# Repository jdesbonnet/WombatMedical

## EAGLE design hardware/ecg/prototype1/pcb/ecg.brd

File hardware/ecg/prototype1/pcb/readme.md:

# ECG PCB

## Notes

JP2 is UART, used for issuing commands, downloading data and upgrading firmware. Firmware updates require the MCU to enter bootloader mode at startup using the DTR, RTS lines (connect DTR to RESET and RTS to ISPEnter pin). Note that connecting to the device with picocom while DTR connected will cause the device to reset on connect. Disconnect RESET line during normal use.

Pin 1 = GND, pin 2 = ISPEnter, pin 3 = Vdd, pin 4 = TXD, pin 5 = RXD, pin 6 = RESET.  

JP4 is a convenient point to access the SPI bus from MCU to ECG front end IC. Pin 1 = DOUT, pin 2 = DIN, pin 3 = SCLK, pin 4 CS. Pin 5, 6 was NC 
on the PCB but on prototype bodge wire was used to connect VCC and GND. 

JP3 analog ECG lines. Pin 1 = RLDOUT, pin 2 = IN1N, pin 3 = IN1P.

JP5 power.

## Bugs

There were some bugs on the board:

1. ADS1929R missing crucial feedback from RLDOUT via 1Mohm resistor with 1.5nF capacitor in parallel with resistor.
Ref datasheet figure 52. Not clear if this bug could have been worked around in software.

2. CLKSEL needs to be tied high to enable internal clock.

3. Coin cell solder mask wrong.

4. It was a mistake not to break out a Serial Wire Debug header.

## Notes for next version

* Move to ARM Cortex-M0+ MCU eg LPC824
* Add SPI flash chip for storage
* Crystal for more accurate off-line time keeping
* Modular radio (allow for RFMxx, or ESP-0x or bluetooth modules)
* Smaller PCB area, thinner (all SMD).
* Use 3.5mm audio jack for 3 wire ECG connector

## Firmware

Firmware is available at this repository:
https://github.com/jdesbonnet/LPC1114_ECG_firmware

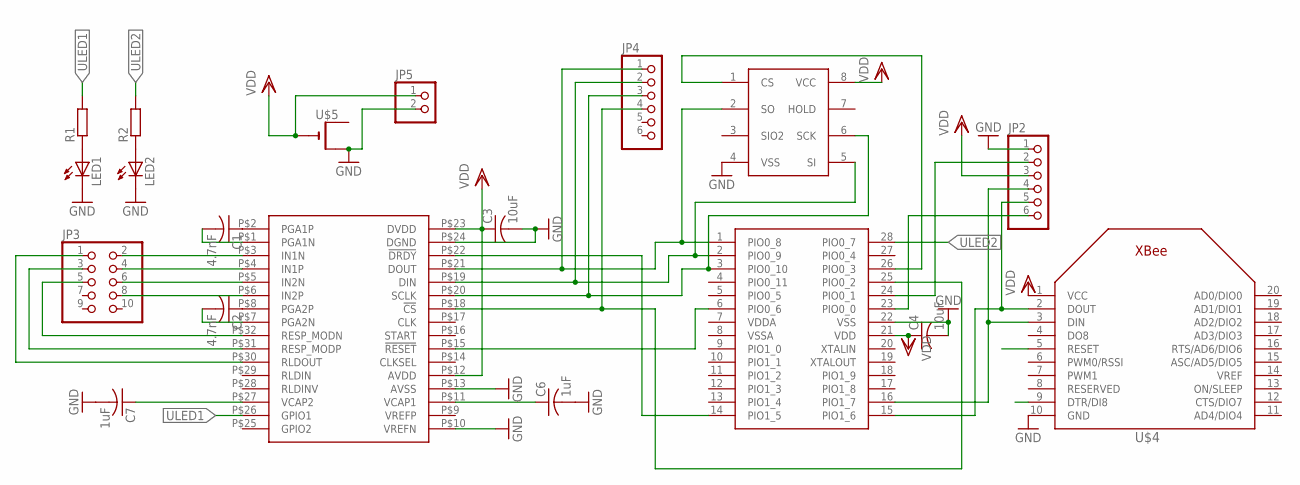
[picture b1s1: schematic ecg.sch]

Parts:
C1, C2: 4.7nF; C0805
C3, C4: 10uF; C0805
C6, C7: 1uF; C0805
JP2, JP4: PINHD-1X6; 1X06
JP3: PINHD-2X5; 2X05
JP5: PINHD-1X2; 1X02
LED1, LED2: LED3MM
R1, R2: R-EU_R0805; R0805
U$1: ADS1929R; TQFP32
U$2: LPC1114FN28; DIL28-6
U$3: 23A1024; DIL08
U$4: XBEE
U$5: CR2032SMT; CR2032-SMD

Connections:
GND: C3.2, C4.2, C6.2, C7.2, JP2.1, JP5.2, LED1.K (C), LED2.K (C), U$1.P$10 (VREFN), U$1.P$13 (AVSS), U$1.P$24 (DGND), U$2.22 (VSS), U$3.4 (VSS), U$4.10 (GND), U$5.+$2 (+1)
unnamed: C1.1, U$1.P$2 (PGA1P)
unnamed: C1.2, U$1.P$1 (PGA1N)
unnamed: C2.1, U$1.P$8 (PGA2P)
unnamed: C2.2, U$1.P$7 (PGA2N)
unnamed: JP4.1, U$1.P$21 (DOUT), U$2.1 (PIO0_8), U$3.2 (SO)
unnamed: JP4.2, U$1.P$19 (DIN), U$2.2 (PIO0_9), U$3.5 (SI)
unnamed: JP4.3, U$1.P$20 (SCLK), U$2.3 (PIO0_10), U$3.6 (SCK)
unnamed: JP4.4, U$1.P$18 (!CS!), U$2.25 (PIO0_2)
unnamed: U$1.P$22 (!DRDY!), U$2.14 (PIO1_5)
unnamed: JP3.2, U$1.P$3 (IN1N)
unnamed: JP3.4, U$1.P$4 (IN1P)
unnamed: JP3.6, U$1.P$5 (IN2N)
unnamed: JP3.8, U$1.P$6 (IN2P)
unnamed: U$1.P$15 (!RESET!), U$2.6 (PIO0_6)
unnamed: JP3.5, U$1.P$32 (RESP_MODN)
unnamed: JP3.3, U$1.P$31 (RESP_MODP)
unnamed: JP3.1, U$1.P$30 (RLDOUT)
unnamed: JP2.6, U$2.23 (PIO0_0)
unnamed: U$2.26 (PIO0_3), U$3.1 (CS)
unnamed: JP2.5, U$2.15 (PIO1_6), U$4.2 (DOUT)
unnamed: JP2.4, U$2.16 (PIO1_7), U$4.3 (DIN)
unnamed: JP2.2, U$2.24 (PIO0_1)
unnamed: C6.1, U$1.P$11 (VCAP1)
unnamed: LED1.A, R1.1
unnamed: LED2.A, R2.1
unnamed: C7.1, U$1.P$27 (VCAP2)
ULED1: R1.2, U$1.P$26 (GPIO1)
ULED2: R2.2, U$2.28 (PIO0_7)
VDD: C3.1, C4.1, JP2.3, JP5.1, U$1.P$12 (AVDD), U$1.P$23 (DVDD), U$2.21 (VDD), U$3.8 (VCC), U$4.1 (VCC), U$5.-

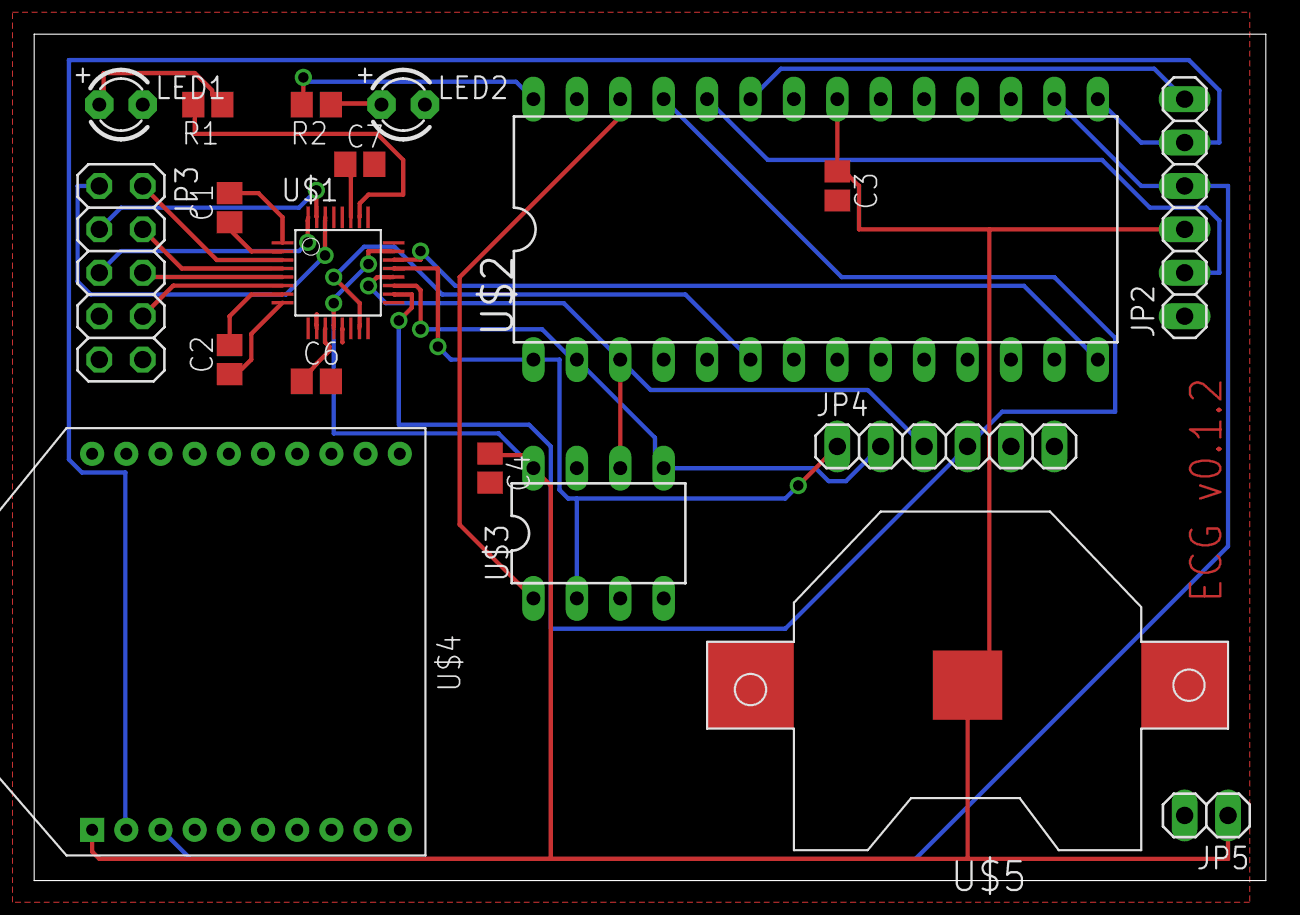
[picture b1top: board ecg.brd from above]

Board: 2 copper layers, 72.1 x 49.5 mm, 19 parts (0 on the bottom side), 30 nets.

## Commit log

2013-04-26 no comment
2013-04-28 First commit.
2013-05-12 First commit of ECG chart widget.
2013-07-13 first commit of board layout and schematics
2013-10-01 PCB v0.1.2, sent to EuroCircuits for fab.
2013-11-29 Move common ecg config code to separate fn
2013-11-29 opt to store and playback ecg
2013-11-29 script to capture and display ecg
2017-03-04 modifications from a few years ago, forgot to check in
2017-03-05 add missing PNG renderings of 2013 ECG prototype
2017-03-05 300dpi version of PCB layout
2017-03-05 some doc on ecg pcb
2017-03-05 updates to readme
2017-03-05 JP2 (UART) header pinout
2017-03-05 more doc on pcb
2017-03-05 missing file
2017-03-05 plot ECG from old data
2017-03-05 Octave/MATLAB script to filter 50Hz mains noise from ECG
2017-03-05 chart to show effect of 50Hz filtering
2017-03-05 script to make gnuplot charts
2017-03-05 add ref to 50Hz filter tutorial video
